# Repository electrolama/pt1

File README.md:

# pt1

**One cable in. A hub, UART, and controllable target power out.**

pt1 is an open-hardware USB multitool for experienced makers doing board bring-up,
firmware development, and field diagnostics. Its approximately 46 × 18 mm PCB
combines:

- a four-port USB 2.0 hub, with one port used by the onboard serial bridge;
- USB-C and USB-A downstream connections;
- a CH343P USB-to-UART interface;
- a protected, software-switchable 5 V rail with fault reporting; and
- a six-pin header exposing UART, USB 2.0, switched power, and ground.

The useful trick is that the serial adapter's modem-control signals do double duty:
**DTR controls target power** and **RI reports an over-current or over-temperature
fault**. That lets a test rig open a console, cycle a target, and detect a power
problem through the same USB connection.

> [!CAUTION]
> pt1 is a USB debugging tool, not a calibrated power meter. Confirm the target's
> voltage and current requirements before connecting it, and do not bridge both
> sides of the downstream USB-C power-selection solder jumper.

## Start here

1. Connect the host to pt1's upstream USB-C port.
2. Wait for the USB hub and CH343 serial port to enumerate.
3. For a UART target, connect target TX → `RX_IN`, target RX → `TX_OUT`, and ground
   → `GND`.
4. Use [Vicuña's pt1 mode](https://lab.electrolama.com/project/vicuna) for an
   integrated terminal, power toggle, and fault indicator—or use the
   [Python example](documentation/examples/power_cycle.py).
5. Read the [getting-started guide](documentation/getting-started.md) before using
   switched power.

## Hardware at a glance

| Function | Implementation | What it gives you |
| --- | --- | --- |
| USB expansion | SL2.1A four-port USB 2.0 hub | Two sockets, one header port, and the internal serial bridge |
| Serial | CH343P USB-to-UART bridge | Target console plus DTR/RI control signals |
| Protected power | RT9742CGJ5 load switch | Current limiting, thermal protection, and active-low fault output |
| Data-line protection | TVS arrays | Transient protection on USB data pairs |
| Mechanical | Three 2 mm mounting holes and printable case | Bench-friendly mounting and enclosure options |

## Documentation

| I want to… | Go to… |
| --- | --- |
| Connect a board safely | [Getting started](documentation/getting-started.md) |
| Identify a connector or header pin | [Pinout and connections](documentation/pinout.md) |
| Automate power cycling and fault detection | [Power control](documentation/power-control.md) |
| Understand the circuit architecture | [Hardware overview](documentation/hardware.md) |
| Print and choose an enclosure | [Enclosures](documentation/enclosures.md) |
| Modify or manufacture the board | [Build and manufacture](documentation/manufacturing.md) |
| Understand revisions and repository layout | [Repository guide](documentation/repository-guide.md) |
| Diagnose a problem | [Troubleshooting](documentation/troubleshooting.md) |
| Propose a change | [Contributing](CONTRIBUTING.md) |

The documentation can also be built as a searchable local site:

```shell
python -m venv .venv
# Windows: .venv\Scripts\activate
# Linux/macOS: source .venv/bin/activate
python -m pip install -r requirements-docs.txt
mkdocs serve
```

## Repository map

```text
pt1/
├── pcba/Rev A2/       KiCad schematic, PCB, and project sources
├── case/Rev A/        Printable STL enclosure variants
├── pinout/            Original pinout generator, data, and source artwork
├── documentation/     Guides, examples, styles, and all new visual assets
├── .github/           Issue forms, pull-request template, and docs automation
├── mkdocs.yml         Documentation-site configuration
└── LICENSES/          CERN-OHL-W-2.0 hardware licence text
```

Current checked-in design revisions are **PCB Rev A2** and **case Rev A**. Source
files are authoritative; generated manufacturing outputs are intentionally not
present in the repository yet.

## Companion software

[Vicuña](https://lab.electrolama.com/project/vicuna) is Electrolama's browser-based
serial monitor and terminal. Its dedicated pt1 mode presents DTR as a clear power
control and RI as a fault indicator instead of exposing generic modem-signal names.

## Project links

- [Published pt1 documentation](https://lab.electrolama.com/project/pt1)
- [Vicuña](https://lab.electrolama.com/project/vicuna)
- [Electrolama](https://electrolama.com)
- [Support and reporting](SUPPORT.md)

## Licence

Hardware source—including schematics, PCB design files, mechanical CAD,
manufacturing files, and other source material required to make or modify the
hardware—is licensed under the [CERN Open Hardware Licence Version 2 — Weakly
Reciprocal](LICENSES/CERN-OHL-W-2.0.txt) (`CERN-OHL-W-2.0`).

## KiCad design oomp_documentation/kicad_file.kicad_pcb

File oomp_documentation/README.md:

# pt1-RevA2

[View the project on GitHub](https://github.com/electrolama/pt1)

pt1-RevA2 is a KiCad project containing 67 extracted component records. The catalogue matcher linked 36 physical placements to OOMP parts.

## Project snapshot

| Item | Count |
| --- | ---: |
| Components | 67 |
| PCB footprints | 37 |
| Mounting and locating holes | 9 |
| Matched OOMP mounting-hole items | 9 |
| Schematic symbols | 64 |
| Matched OOMP components | 36 |
| Unmatched physical components | 0 |
| Front-side placements | 33 |
| Back-side placements | 0 |
| Project version | `current` |
| Git ref | `main` |

## Board

- Approximate size: **18.0 mm × 46.0 mm**
- Outline source: `KiCad Edge.Cuts`
- Placement drawing: [view `board.svg`](https://github.com/oomlout/oomp_electronic_version_5/blob/main/parts/oomp_project_github_electrolama_pt1_current/generated_data/src/board.svg)
- PNG placement drawing: [view `board.png`](https://github.com/oomlout/oomp_electronic_version_5/blob/main/parts/oomp_project_github_electrolama_pt1_current/generated_data/src/board.png)
- 300-pixel placement preview: [view `board_300.png`](https://github.com/oomlout/oomp_electronic_version_5/blob/main/parts/oomp_project_github_electrolama_pt1_current/generated_data/src/board_300.png)
- Placement drawing with pin names: [view `board_pins.svg`](https://github.com/oomlout/oomp_electronic_version_5/blob/main/parts/oomp_project_github_electrolama_pt1_current/generated_data/src/board_pins.svg)
- PNG drawing with pin names: [view `board_pins.png`](https://github.com/oomlout/oomp_electronic_version_5/blob/main/parts/oomp_project_github_electrolama_pt1_current/generated_data/src/board_pins.png)
- 300-pixel pin preview: [view `board_pins_300.png`](https://github.com/oomlout/oomp_electronic_version_5/blob/main/parts/oomp_project_github_electrolama_pt1_current/generated_data/src/board_pins_300.png)
- Bottom placement drawing: [view `board_bottom.svg`](https://github.com/oomlout/oomp_electronic_version_5/blob/main/parts/oomp_project_github_electrolama_pt1_current/generated_data/src/board_bottom.svg)
- Bottom PNG placement drawing: [view `board_bottom.png`](https://github.com/oomlout/oomp_electronic_version_5/blob/main/parts/oomp_project_github_electrolama_pt1_current/generated_data/src/board_bottom.png)
- 300-pixel bottom preview: [view `board_bottom_300.png`](https://github.com/oomlout/oomp_electronic_version_5/blob/main/parts/oomp_project_github_electrolama_pt1_current/generated_data/src/board_bottom_300.png)
- Bottom placement drawing with pin names: [view `board_pins_bottom.svg`](https://github.com/oomlout/oomp_electronic_version_5/blob/main/parts/oomp_project_github_electrolama_pt1_current/generated_data/src/board_pins_bottom.svg)
- Bottom PNG drawing with pin names: [view `board_pins_bottom.png`](https://github.com/oomlout/oomp_electronic_version_5/blob/main/parts/oomp_project_github_electrolama_pt1_current/generated_data/src/board_pins_bottom.png)
- 300-pixel bottom pin preview: [view `board_pins_bottom_300.png`](https://github.com/oomlout/oomp_electronic_version_5/blob/main/parts/oomp_project_github_electrolama_pt1_current/generated_data/src/board_pins_bottom_300.png)
- Mechanical drawing: [view `board_mechanical.svg`](https://github.com/oomlout/oomp_electronic_version_5/blob/main/parts/oomp_project_github_electrolama_pt1_current/generated_data/src/board_mechanical.svg)
- Mechanical PNG: [view `board_mechanical.png`](https://github.com/oomlout/oomp_electronic_version_5/blob/main/parts/oomp_project_github_electrolama_pt1_current/generated_data/src/board_mechanical.png)
- 300-pixel mechanical preview: [view `board_mechanical_300.png`](https://github.com/oomlout/oomp_electronic_version_5/blob/main/parts/oomp_project_github_electrolama_pt1_current/generated_data/src/board_mechanical_300.png)
- Self-contained interactive explorer: [download `board_explorer.html`](https://github.com/oomlout/oomp_electronic_version_5/blob/main/parts/oomp_project_github_electrolama_pt1_current/generated_data/board_explorer.html)

## Board with pins

## Bottom board with pins

The bottom view is mirrored horizontally so it is shown as viewed from beneath the assembled board.

## Mechanical layer

The table uses a board-relative origin at the minimum X/Y point of `Edge.Cuts`. This point is shown as **0,0** in the mechanical drawing; X increases right and Y increases down. Original KiCad coordinates are retained alongside it.

| OOMP reference | Source | Name | Classification | Role | Drill size | Board X (mm) | Board Y (mm) | OOMP part |
| --- | --- | --- | --- | --- | --- | ---: | ---: | --- |
| `MH1` | `CON1` | Mounting Hole 0.65 mm Round Unplated | `mechanical / mounting_hole / 0_65_mm / round / unplated` | locating | diameter 0.65 mm | 6.110 | 41.190 | [`mechanical_mounting_hole_0_65_mm_round_unplated`](https://github.com/oomlout/oomp_electronic_version_5/tree/main/parts/mechanical_mounting_hole_0_65_mm_round_unplated) |
| `MH2` | `CON1` | Mounting Hole 0.65 mm Round Unplated | `mechanical / mounting_hole / 0_65_mm / round / unplated` | locating | diameter 0.65 mm | 11.890 | 41.190 | [`mechanical_mounting_hole_0_65_mm_round_unplated`](https://github.com/oomlout/oomp_electronic_version_5/tree/main/parts/mechanical_mounting_hole_0_65_mm_round_unplated) |
| `MH3` | `CON2` | Mounting Hole 0.65 mm Round Unplated | `mechanical / mounting_hole / 0_65_mm / round / unplated` | locating | diameter 0.65 mm | 4.810 | 15.110 | [`mechanical_mounting_hole_0_65_mm_round_unplated`](https://github.com/oomlout/oomp_electronic_version_5/tree/main/parts/mechanical_mounting_hole_0_65_mm_round_unplated) |
| `MH4` | `CON2` | Mounting Hole 0.65 mm Round Unplated | `mechanical / mounting_hole / 0_65_mm / round / unplated` | locating | diameter 0.65 mm | 4.810 | 20.890 | [`mechanical_mounting_hole_0_65_mm_round_unplated`](https://github.com/oomlout/oomp_electronic_version_5/tree/main/parts/mechanical_mounting_hole_0_65_mm_round_unplated) |
| `MH5` | `CON3` | Mounting Hole 0.8 mm Round Plated | `mechanical / mounting_hole / 0_8_mm / round / plated` | shield_mount | diameter 0.8 mm | 2.600 | 1.635 | [`mechanical_mounting_hole_0_8_mm_round_plated`](https://github.com/oomlout/oomp_electronic_version_5/tree/main/parts/mechanical_mounting_hole_0_8_mm_round_plated) |
| `MH6` | `CON3` | Mounting Hole 0.8 mm Round Plated | `mechanical / mounting_hole / 0_8_mm / round / plated` | shield_mount | diameter 0.8 mm | 15.400 | 1.635 | [`mechanical_mounting_hole_0_8_mm_round_plated`](https://github.com/oomlout/oomp_electronic_version_5/tree/main/parts/mechanical_mounting_hole_0_8_mm_round_plated) |
| `MH7` | `UNK_HOLE_0` | Mounting Hole 2 mm Round Unplated | `mechanical / mounting_hole / 2_mm / round / unplated` | mounting | diameter 2 mm | 2.250 | 11.375 | [`mechanical_mounting_hole_2_mm_round_unplated`](https://github.com/oomlout/oomp_electronic_version_5/tree/main/parts/mechanical_mounting_hole_2_mm_round_unplated) |
| `MH8` | `UNK_HOLE_1` | Mounting Hole 2 mm Round Unplated | `mechanical / mounting_hole / 2_mm / round / unplated` | mounting | diameter 2 mm | 15.750 | 42.500 | [`mechanical_mounting_hole_2_mm_round_unplated`](https://github.com/oomlout/oomp_electronic_version_5/tree/main/parts/mechanical_mounting_hole_2_mm_round_unplated) |
| `MH9` | `UNK_HOLE_2` | Mounting Hole 2 mm Round Unplated | `mechanical / mounting_hole / 2_mm / round / unplated` | mounting | diameter 2 mm | 2.250 | 42.500 | [`mechanical_mounting_hole_2_mm_round_unplated`](https://github.com/oomlout/oomp_electronic_version_5/tree/main/parts/mechanical_mounting_hole_2_mm_round_unplated) |

## Bill of materials

| References | Quantity | Description | Value | Footprint | OOMP part |
| --- | ---: | --- | --- | --- | --- |
| C1 | 1 | electronic capacitor 0402 10 nano farad | 10n | `_PKG_C_0402` | [`electronic_capacitor_0402_10_nano_farad`](https://github.com/oomlout/oomp_electronic_version_5/tree/main/parts/electronic_capacitor_0402_10_nano_farad) |
| C2, C6, C9, C10, C14 | 5 | electronic capacitor 0402 100 nano farad | 100n | `_PKG_C_0402` | [`electronic_capacitor_0402_100_nano_farad`](https://github.com/oomlout/oomp_electronic_version_5/tree/main/parts/electronic_capacitor_0402_100_nano_farad) |
| C3, C4, C7, C8 | 4 | electronic capacitor 1206 47 micro farad | 47u | `_PKG_C_1206` | [`electronic_capacitor_1206_47_micro_farad`](https://github.com/oomlout/oomp_electronic_version_5/tree/main/parts/electronic_capacitor_1206_47_micro_farad) |
| C5, C11, C12, C13 | 4 | electronic capacitor 0402 10 micro farad | 10u | `_PKG_C_0402` | [`electronic_capacitor_0402_10_micro_farad`](https://github.com/oomlout/oomp_electronic_version_5/tree/main/parts/electronic_capacitor_0402_10_micro_farad) |
| CON1, CON2 | 2 | electronic connector usb c surface mount 16 pin korean hroparts elec typec31m12 | USB-C | `USBC_C-31-M-12` | [`electronic_connector_usb_c_surface_mount_16_pin_korean_hroparts_elec_typec31m12`](https://github.com/oomlout/oomp_electronic_version_5/tree/main/parts/electronic_connector_usb_c_surface_mount_16_pin_korean_hroparts_elec_typec31m12) |
| CON3 | 1 | electronic connector usb a surface mount 4 pin shenzhen jing tuo jin electronics 912121a2023s10100 | USB-A Female | `JING_912-121A2023S10100` | [`electronic_connector_usb_a_surface_mount_4_pin_shenzhen_jing_tuo_jin_electronics_912121a2023s10100`](https://github.com/oomlout/oomp_electronic_version_5/tree/main/parts/electronic_connector_usb_a_surface_mount_4_pin_shenzhen_jing_tuo_jin_electronics_912121a2023s10100) |
| D1, D2 | 2 | electronic diode tvs array sot 23 6 protek srv054pt7 | SRV05-4-P-T7 | `SOT95P280X145-6N` | [`electronic_diode_tvs_array_sot_23_6_protek_srv054pt7`](https://github.com/oomlout/oomp_electronic_version_5/tree/main/parts/electronic_diode_tvs_array_sot_23_6_protek_srv054pt7) |
| IC1 | 1 | electronic ic qfn 16 3 mm x 3 mm converter usb to serial converter wch ch343p | CH343P | `QFN16_L3.0-W3.0-P0.50-EP1.7` | [`electronic_ic_qfn_16_3_mm_x_3_mm_converter_usb_to_serial_converter_wch_ch343p`](https://github.com/oomlout/oomp_electronic_version_5/tree/main/parts/electronic_ic_qfn_16_3_mm_x_3_mm_converter_usb_to_serial_converter_wch_ch343p) |
| IC2 | 1 | electronic ic sop 16 controller usb hub controller 4 port corechips sl21a | SL2.1A | `SOIC127P604X185-16N` | [`electronic_ic_sop_16_controller_usb_hub_controller_4_port_corechips_sl21a`](https://github.com/oomlout/oomp_electronic_version_5/tree/main/parts/electronic_ic_sop_16_controller_usb_hub_controller_4_port_corechips_sl21a) |
| IC3 | 1 | electronic ic sot 23 6 logic configurable multi function gate texas instruments sn74lvc1g57dbvr | SN74LVC1G57DBV | `SOT95P280X145-6N` | [`electronic_ic_sot_23_6_logic_configurable_multi_function_gate_texas_instruments_sn74lvc1g57dbvr`](https://github.com/oomlout/oomp_electronic_version_5/tree/main/parts/electronic_ic_sot_23_6_logic_configurable_multi_function_gate_texas_instruments_sn74lvc1g57dbvr) |
| IC4 | 1 | electronic ic tsot 23 5 power management high side power switch with flag richtek rt9742cgj5 | RT9742CGJ5 | `_PKG_SOT23-5` | [`electronic_ic_tsot_23_5_power_management_high_side_power_switch_with_flag_richtek_rt9742cgj5`](https://github.com/oomlout/oomp_electronic_version_5/tree/main/parts/electronic_ic_tsot_23_5_power_management_high_side_power_switch_with_flag_richtek_rt9742cgj5) |
| J1 | 1 | electronic connector header 2 54 mm pitch through hole 6 pin |  | `1X06_LOCK` | [`electronic_connector_header_2_54_mm_pitch_through_hole_6_pin`](https://github.com/oomlout/oomp_electronic_version_5/tree/main/parts/electronic_connector_header_2_54_mm_pitch_through_hole_6_pin) |
| L1 | 1 | electronic ferrite bead 0805 220 ohm 2 amp murata blm21pg221sn1d | FB, 2A | `_PKG_C_0805` | [`electronic_ferrite_bead_0805_220_ohm_2_amp_murata_blm21pg221sn1d`](https://github.com/oomlout/oomp_electronic_version_5/tree/main/parts/electronic_ferrite_bead_0805_220_ohm_2_amp_murata_blm21pg221sn1d) |
| LED1 | 1 | electronic led 0603 green | Green | `_PKG_LED_0603` | [`electronic_led_0603_green`](https://github.com/oomlout/oomp_electronic_version_5/tree/main/parts/electronic_led_0603_green) |
| R1, R2 | 2 | electronic resistor 0402 5100 ohm | 5k1 | `_PKG_R_0402` | [`electronic_resistor_0402_5100_ohm`](https://github.com/oomlout/oomp_electronic_version_5/tree/main/parts/electronic_resistor_0402_5100_ohm) |
| R3 | 1 | electronic resistor 0402 510000 ohm | 510k | `_PKG_R_0402` | [`electronic_resistor_0402_510000_ohm`](https://github.com/oomlout/oomp_electronic_version_5/tree/main/parts/electronic_resistor_0402_510000_ohm) |
| R4 | 1 | electronic resistor 0402 2200 ohm | 2k2 | `_PKG_R_0402` | [`electronic_resistor_0402_2200_ohm`](https://github.com/oomlout/oomp_electronic_version_5/tree/main/parts/electronic_resistor_0402_2200_ohm) |
| R5, R6 | 2 | electronic resistor 0402 100000 ohm | 100k | `_PKG_R_0402` | [`electronic_resistor_0402_100000_ohm`](https://github.com/oomlout/oomp_electronic_version_5/tree/main/parts/electronic_resistor_0402_100000_ohm) |
| XT1 | 1 | electronic crystal 3225 surface mount 4 pin 12 mhz 20 pf | 12MHz | `XTAL-4P-3225` | [`electronic_crystal_3225_surface_mount_4_pin_12_mhz_20_pf`](https://github.com/oomlout/oomp_electronic_version_5/tree/main/parts/electronic_crystal_3225_surface_mount_4_pin_12_mhz_20_pf) |

## Main nets

| Net | Pads | Components |
| --- | ---: | --- |
| `GND` | 51 | C1, C2, C3, C4, C5, C6, C7, C8, C9, C10, C11, C12, C13, C14, CON1, CON2, CON3, D1, D2, IC1, IC2, IC3, IC4, J1, LED1, R1, R2, R5, XT1 |
| `VUSB` | 17 | C2, C3, C4, C6, C10, C13, D1, D2, IC1, IC2, IC3, IC4, L1, R3, SJ1 |
| `VUSB_SW_OUT` | 8 | C7, C8, C9, CON3, IC4, J1, R4, SJ1 |
| `SER_3V3` | 4 | C14, IC1, R6 |
| `USB1_N` | 4 | CON2, D1, IC2 |
| `USB1_P` | 4 | CON2, D1, IC2 |
| `USB_UP_N` | 4 | CON1, D2, IC2 |
| `USB_UP_P` | 4 | CON1, D2, IC2 |
| `VUSB_IN` | 4 | C1, CON1, L1 |
| `N$3` | 3 | CON2, SJ1 |
| `N$6` | 3 | C5, IC3, R3 |
| `SER_RI` | 3 | IC1, IC4, R6 |
| `SW_EN` | 3 | IC3, IC4, R5 |
| `USB2_N` | 3 | CON3, D1, IC2 |
| `USB2_P` | 3 | CON3, D1, IC2 |
| `USB3_N` | 3 | D2, IC2, J1 |
| `USB3_P` | 3 | D2, IC2, J1 |
| `N$1` | 2 | IC2, XT1 |
| `N$13` | 2 | C11, IC2 |
| `N$14` | 2 | C12, IC2 |

## Design notes

- The extracted board outline is approximately 18.0 mm by 46.0 mm.
- Placement data contains 33 front-side and 0 back-side components.

## Review notes

- The extractor reports 21 named-net comparisons that differ between schematic and PCB data.

- Part identities needing a manufacturer/LCSC decision: [`lcsc_review.yaml`](https://github.com/oomlout/oomp_electronic_version_5/blob/main/parts/oomp_project_github_electrolama_pt1_current/generated_data/lcsc_review.yaml)
- Browser-only research and datasheet queue: [`browser_research_queue.md`](https://github.com/oomlout/oomp_electronic_version_5/blob/main/parts/oomp_project_github_electrolama_pt1_current/generated_data/browser_research_queue.md)

## Generated source bundle

- Project image assets: [`generated_data/src`](https://github.com/oomlout/oomp_electronic_version_5/tree/main/parts/oomp_project_github_electrolama_pt1_current/generated_data/src)
- Copied component source manifest: `project_source/manifest.yaml` (generated locally and ignored by Git)
- Matched OOMP source parts copied: 20

## Source files

- Schematic: `kicad_file.kicad_sch`
- PCB: `kicad_file.kicad_pcb`

---

Generated deterministically by `kicad_agents.project_summary_agent`; no LLM-authored content is used.

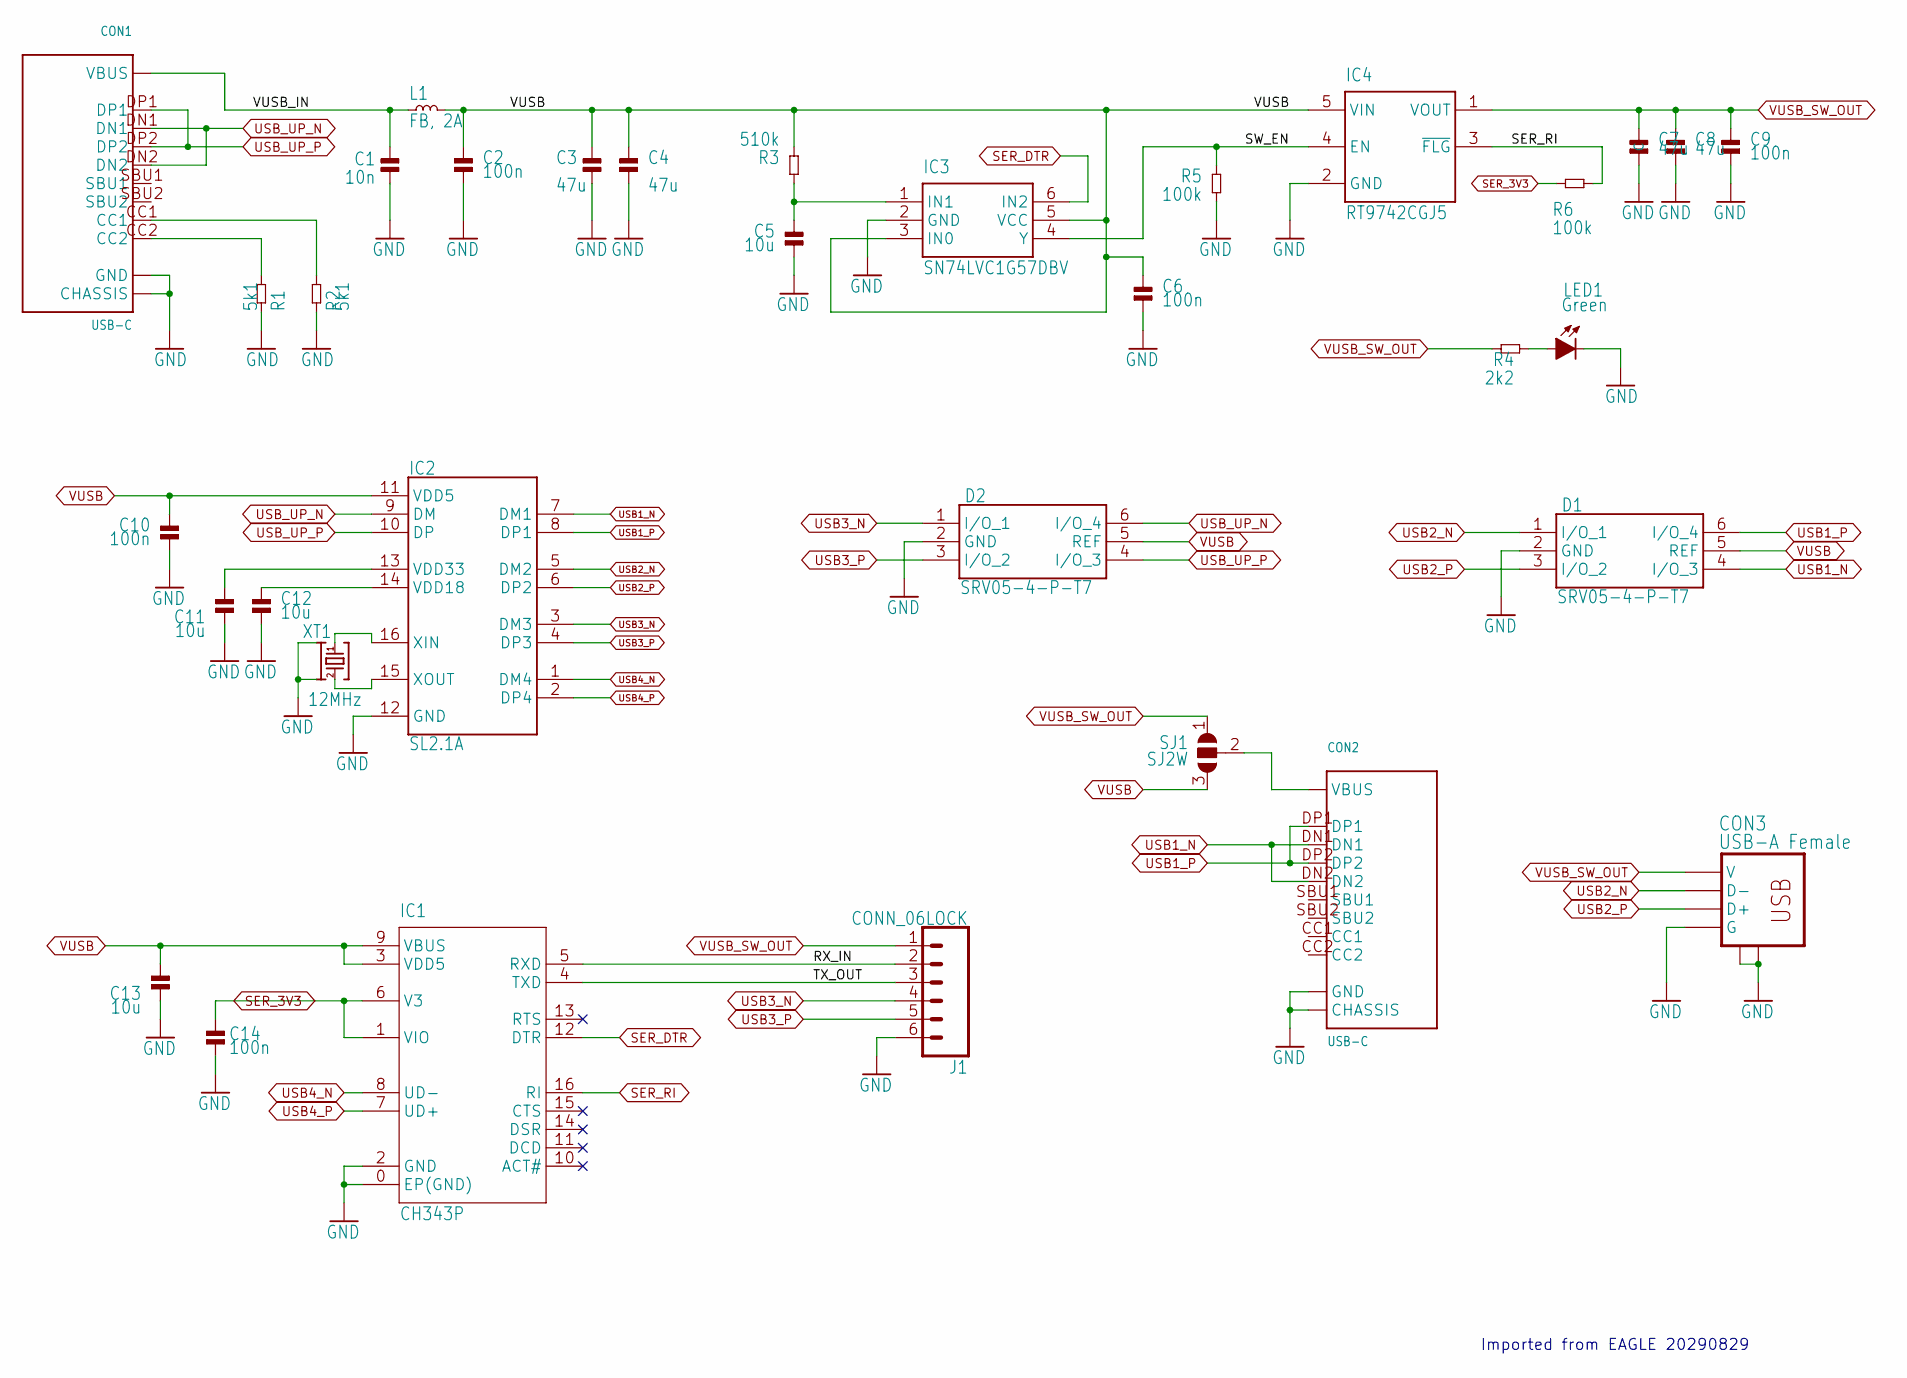
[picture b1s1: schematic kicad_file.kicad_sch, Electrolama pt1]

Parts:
C1: 10n; _PKG_C_0402; MPN CL05B103KB5NNNC; JLCASSY C15195
C2, C6, C9, C10, C14: 100n; _PKG_C_0402; MPN CL05B104KO5NNNC; JLCASSY C1525
C3, C4, C7, C8: 47u; _PKG_C_1206; MPN CL31A476MPHNNNE; JLCASSY C96123
C5, C11, C12, C13: 10u; _PKG_C_0402; MPN CL05A106MQ5NUNC; JLCASSY C15525
CON1, CON2: USB-C; USBC_C-31-M-12; MPN TYPE-C-31-M-12; JLCASSY C165948
CON3: USB-A Female; JING_912-121A2023S10100; MPN 912-121A2023S10100; JLCASSY C42428
D1, D2: SRV05-4-P-T7; SOT95P280X145-6N; MANUFACTURER_PART_NUMBER SRV05-4-P-T7; JLCASSY C85364
IC1: CH343P; QFN16_L3.0-W3.0-P0.50-EP1.7; MPN CH343P; JLCASSY C2846043
IC2: SL2.1A; SOIC127P604X185-16N; MANUFACTURER_PART_NUMBER SL2.1A; JLCASSY C192893
IC3: SN74LVC1G57DBV; SOT95P280X145-6N; MANUFACTURER_PART_NUMBER SN74LVC1G57DBVRG4; MOUSER_PART_NUMBER 595-74LVC1G57DBVRG4
IC4: RT9742CGJ5; _PKG_SOT23-5; MPN RT9742CGJ5; JLCASSY C250546
J1: CONN_06LOCK; 1X06_LOCK
L1: FB, 2A; _PKG_C_0805; MPN BLM21PG221SN1D; JLCASSY C85840
LED1: Green; _PKG_LED_0603; MPN 19-217/GHC-YR1S2/3T; JLCASSY C72043
R1, R2: 5k1; _PKG_R_0402; MPN AC0402FR-075K1L; JLCASSY C144745
R3: 510k; _PKG_R_0402; MPN 0402WGF5103TCE; JLCASSY C11616
R4: 2k2; _PKG_R_0402; MPN 0402WGF2201TCE; JLCASSY C25879
R5, R6: 100k; _PKG_R_0402; MPN 0402WGF1003TCE; JLCASSY C25741
SJ1: SJ2W; SJ_2
XT1: 12MHz; XTAL-4P-3225; MPN X322512MSB4SI; JLCASSY C9002

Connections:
GND: C1.1, C2.1, C3.2, C4.2, C5.1, C6.1, C7.1, C8.1, C9.1, C10.1, C11.1, C12.1, C13.1, C14.1, CON1.GND@1 (GND), CON1.GND@2 (GND), CON1.P$1 (CHASSIS), CON1.P$2 (CHASSIS), CON1.P$3 (CHASSIS), CON1.P$4 (CHASSIS), CON1.P$5 (CHASSIS), CON1.P$6 (CHASSIS), CON1.P$7 (CHASSIS), CON1.P$8 (CHASSIS), CON2.GND@1 (GND), CON2.GND@2 (GND), CON2.P$1 (CHASSIS), CON2.P$2 (CHASSIS), CON2.P$3 (CHASSIS), CON2.P$4 (CHASSIS), CON2.P$5 (CHASSIS), CON2.P$6 (CHASSIS), CON2.P$7 (CHASSIS), CON2.P$8 (CHASSIS), CON3.GND (G), CON3.P$5 (SHIELD1), CON3.P$6 (SHIELD2), D1.2 (GND), D2.2 (GND), IC1.0 (EP(GND)), IC1.2 (GND), IC2.12 (GND), IC3.2 (GND), IC4.2 (GND), J1.6, LED1.C, R1.1, R2.1, R5.2, XT1.2, XT1.4
unnamed: IC2.16 (XIN), XT1.1
unnamed: CON2.VBUS@1 (VBUS), CON2.VBUS@2 (VBUS), SJ1.2
unnamed: LED1.A, R4.1
unnamed: IC2.15 (XOUT), XT1.3
unnamed: C5.2, IC3.1 (IN1), R3.2
unnamed: CON1.CC1, R2.2
unnamed: CON1.CC2, R1.2
unnamed: C11.2, IC2.13 (VDD33)
unnamed: C12.2, IC2.14 (VDD18)
RX_IN: IC1.5 (RXD), J1.2
SER_3V3: C14.2, IC1.1 (VIO), IC1.6 (V3), R6.1
SER_DTR: IC1.12 (DTR), IC3.6 (IN2)
SER_RI: IC1.16 (RI), IC4.3 (~FLG), R6.2
SW_EN: IC3.4 (Y), IC4.4 (EN), R5.1
TX_OUT: IC1.4 (TXD), J1.3
USB1_N: CON2.DN1, CON2.DN2, D1.4 (I/O_3), IC2.7 (DM1)
USB1_P: CON2.DP1, CON2.DP2, D1.6 (I/O_4), IC2.8 (DP1)
USB2_N: CON3.DM (D-), D1.1 (I/O_1), IC2.5 (DM2)
USB2_P: CON3.DP (D+), D1.3 (I/O_2), IC2.6 (DP2)
USB3_N: D2.1 (I/O_1), IC2.3 (DM3), J1.4
USB3_P: D2.3 (I/O_2), IC2.4 (DP3), J1.5
USB4_N: IC1.8 (UD-), IC2.1 (DM4)
USB4_P: IC1.7 (UD+), IC2.2 (DP4)
USB_UP_N: CON1.DN1, CON1.DN2, D2.6 (I/O_4), IC2.9 (DM)
USB_UP_P: CON1.DP1, CON1.DP2, D2.4 (I/O_3), IC2.10 (DP)
VUSB: C2.2, C3.1, C4.1, C6.2, C10.2, C13.2, D1.5 (REF), D2.5 (REF), IC1.3 (VDD5), IC1.9 (VBUS), IC2.11 (VDD5), IC3.3 (IN0), IC3.5 (VCC), IC4.5 (VIN), L1.2, R3.1, SJ1.3
VUSB_IN: C1.2, CON1.VBUS@1 (VBUS), CON1.VBUS@2 (VBUS), L1.1
VUSB_SW_OUT: C7.2, C8.2, C9.2, CON3.VBUS (V), IC4.1 (VOUT), J1.1, R4.2, SJ1.1

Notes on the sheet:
Imported from EAGLE 20290829

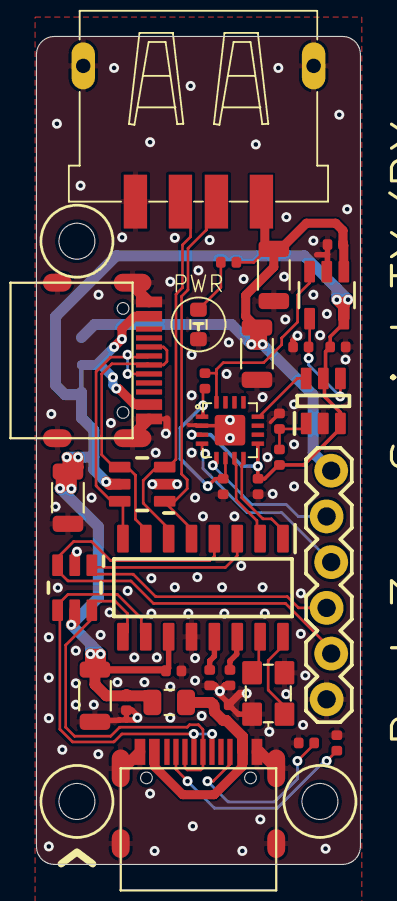
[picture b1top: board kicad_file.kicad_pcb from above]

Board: 2 copper layers, 18.0 x 46.0 mm, 37 parts (1 on the bottom side), 29 nets.

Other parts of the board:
UNK_HOLE_0: dummyfp0
UNK_HOLE_1: dummyfp1
UNK_HOLE_2: dummyfp2
